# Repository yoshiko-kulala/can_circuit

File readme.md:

# ロボット用can通信基板
このリポジトリはcan通信を用いてロボットのセンサやアクチュエータと通信・制御するための基板が置いてあります。  

各基板ごとに回路図、kicadプロジェクトデータ、サンプルプログラムが含まれます。  
自由に複製してロボットに用いることが出来ます。

can通信のid、内容については下記の各項目で示します。
通信速度は1Mbpsです。

## bumperboard
デジタルのスイッチとADCの信号を読み取ることが出来ます。  
デジタル信号が4つ、ADCは8bitが8チャネルあります。  
メインMCUにはteensy3.2を使用、can通信の通信内容は以下の通りです。  
### 0x001
| buf[1] | 中身 | 備考 |
| -------- | -------- | -------- |
| buf[0] | デジタル信号 | 4つの入力の論理和 |
### 0x003
| buf[8] | 中身 | 備考 |
| -------- | -------- | -------- |
| buf[0] | A0 | 0~255 |
| buf[1] | A1 |  |
| buf[2] | A2 |  |
| buf[3] | A3 |  |
| buf[4] | A4 |  |
| buf[5] | A5 |  |
| buf[6] | A6 |  |
| buf[7] | A7 |  |

## encoderboard  
インクリメントエンコーダを読み取り、回転速度と積分量を返します。  
エンコーダは最大3つまで搭載できます。
MCUにはstm32f303k8を使用し、ハードウェアデコーダを用いてエンコーダの読み取りを行っています。
can通信の内容は以下の通りです。
### 0x301
| buf[8] | 中身 | 備考 |
| -------- | -------- | -------- |
| buf[0] | エンコーダ0のカウント下8bit | 速度は10bit |
| buf[1] | エンコーダ0のカウント上2bitとエンコーダ1のカウント下6bit |  |
| buf[2] | エンコーダ1のカウント下4bitとエンコーダ2のカウント下4bit |  |
| buf[3] | エンコーダ2のカウント下6bit |  |
| buf[4] | 未使用 |  |
| buf[5] | 未使用 |  |
| buf[6] | 未使用 |  |
| buf[7] | 未使用 |  |
### 0x302
| buf[8] | 中身 | 備考 |
| -------- | -------- | -------- |
| buf[0] | エンコーダ0のカウント下8bit | 上下合成して0~65536 |
| buf[1] | エンコーダ0のカウント上8bit |  |
| buf[2] | エンコーダ1のカウント下8bit | 上下合成して0~65536 |
| buf[3] | エンコーダ1のカウント上8bit |  |
| buf[4] | エンコーダ2のカウント下8bit | 上下合成して0~65536 |
| buf[5] | エンコーダ2のカウント上8bit |  |
| buf[6] | 未使用 |  |
| buf[7] | 未使用 |  |

## purin_main_board  
ブザーやジャイロ、コントローラ用の通信口を持った基板  
モータドライバとも接続可能で足回りの駆動系と通信することが出来る  
DJIのDR16と接続することでコントローラとの通信も可能
この基板についてはデバッグ用のcan受信プログラムが書かれている。使途に合わせて自由な内容を受信し、それに合わせてブザーを鳴らしたりモータを動かすことが可能である。

## RIOboard  
myRIOと接続し、can通信とmyRIOをつなげる基板  
myRIOとはGPIO4つとuartで接続されている。
また、myRIOからスレーブコントローラ用へのUSBコネクタも内包している。
この基板もmyRIOからの信号に合わせて自由に通信内容を決めることが出来る。

## stepperboard  
ステッピングモータを駆動させるための基板  
L6470とSPI通信を行い、最大3つのステッピングモータを駆動可能  
電源供給用のコネクタやリミットスイッチの入力コネクタも実装済  
サーボを1つまで接続し動作させることが出来る  
can通信の内容は以下の通り  
### 0x2F1
| buf[8] | 中身 | 備考 |
| -------- | -------- | -------- |
| buf[0] | 現在のx軸(左右)の下8bit | x上限は4374  センターは2768 |
| buf[1] | 現在のx軸(左右)の上8bit | 下限が左 |
| buf[2] | 現在のy軸(上下)の下8bit | y上限は4050 |
| buf[3] | 現在のy軸(上下)の上8bit | 下限が上 |
| buf[4] | 現在のz軸(前後)の下8bit | z上限は31500 |
| buf[5] | 現在のz軸(前後)の上8bit | 下限が後 |
| buf[6] | ハンド | 1で閉じてる、0で開いてる |
| buf[7] | 未使用 |  |
### 0x2F2
| buf[8] | 中身 | 備考 |
| -------- | -------- | -------- |
| buf[0] | 目標のx軸(左右)の下8bit | x上限は4374  センターは2768 |
| buf[1] | 目標のx軸(左右)の上8bit | 下限が左 |
| buf[2] | 目標のy軸(上下)の下8bit | y上限は4050 |
| buf[3] | 目標のy軸(上下)の上8bit | 下限が上 |
| buf[4] | 目標のz軸(前後)の下8bit | z上限は31500 |
| buf[5] | 目標のz軸(前後)の上8bit | 下限が後 |
| buf[6] | ホーム復帰 | 1でホーム復帰 |
| buf[7] | 未使用 |  |
### 0x2F3
msg.len=1
| buf[1] | 中身 | 備考 |
| -------- | -------- | -------- |
| buf[0] | ハンド開閉 | 0が閉じている、1が開いてる |

## UIboard  
デジタルの信号入力が4つ、ws2812bというマイコン内蔵RGBLEDの制御信号を出すことが出来る  
非常停止スイッチが取り付けられることを想定してcanのidは0となっており最優先で信号が送られる。  
通信内容は以下の通り。  
### 0x000
| buf[8] | 中身 | 備考 |
| -------- | -------- | -------- |
| buf[0] | 状態 | 現在のライトの色 |
| buf[1] | 非常停止スイッチ | 押下状態で0 |
| buf[2] | リセットスイッチ | 押下状態で0 |
| buf[3] | 起動スイッチ | 押下状態で0 |
| buf[4] | 空き | 押下状態で0 |
| buf[5] | 未使用 |  |
| buf[6] | 未使用 |  |
| buf[7] | 未使用 |  |

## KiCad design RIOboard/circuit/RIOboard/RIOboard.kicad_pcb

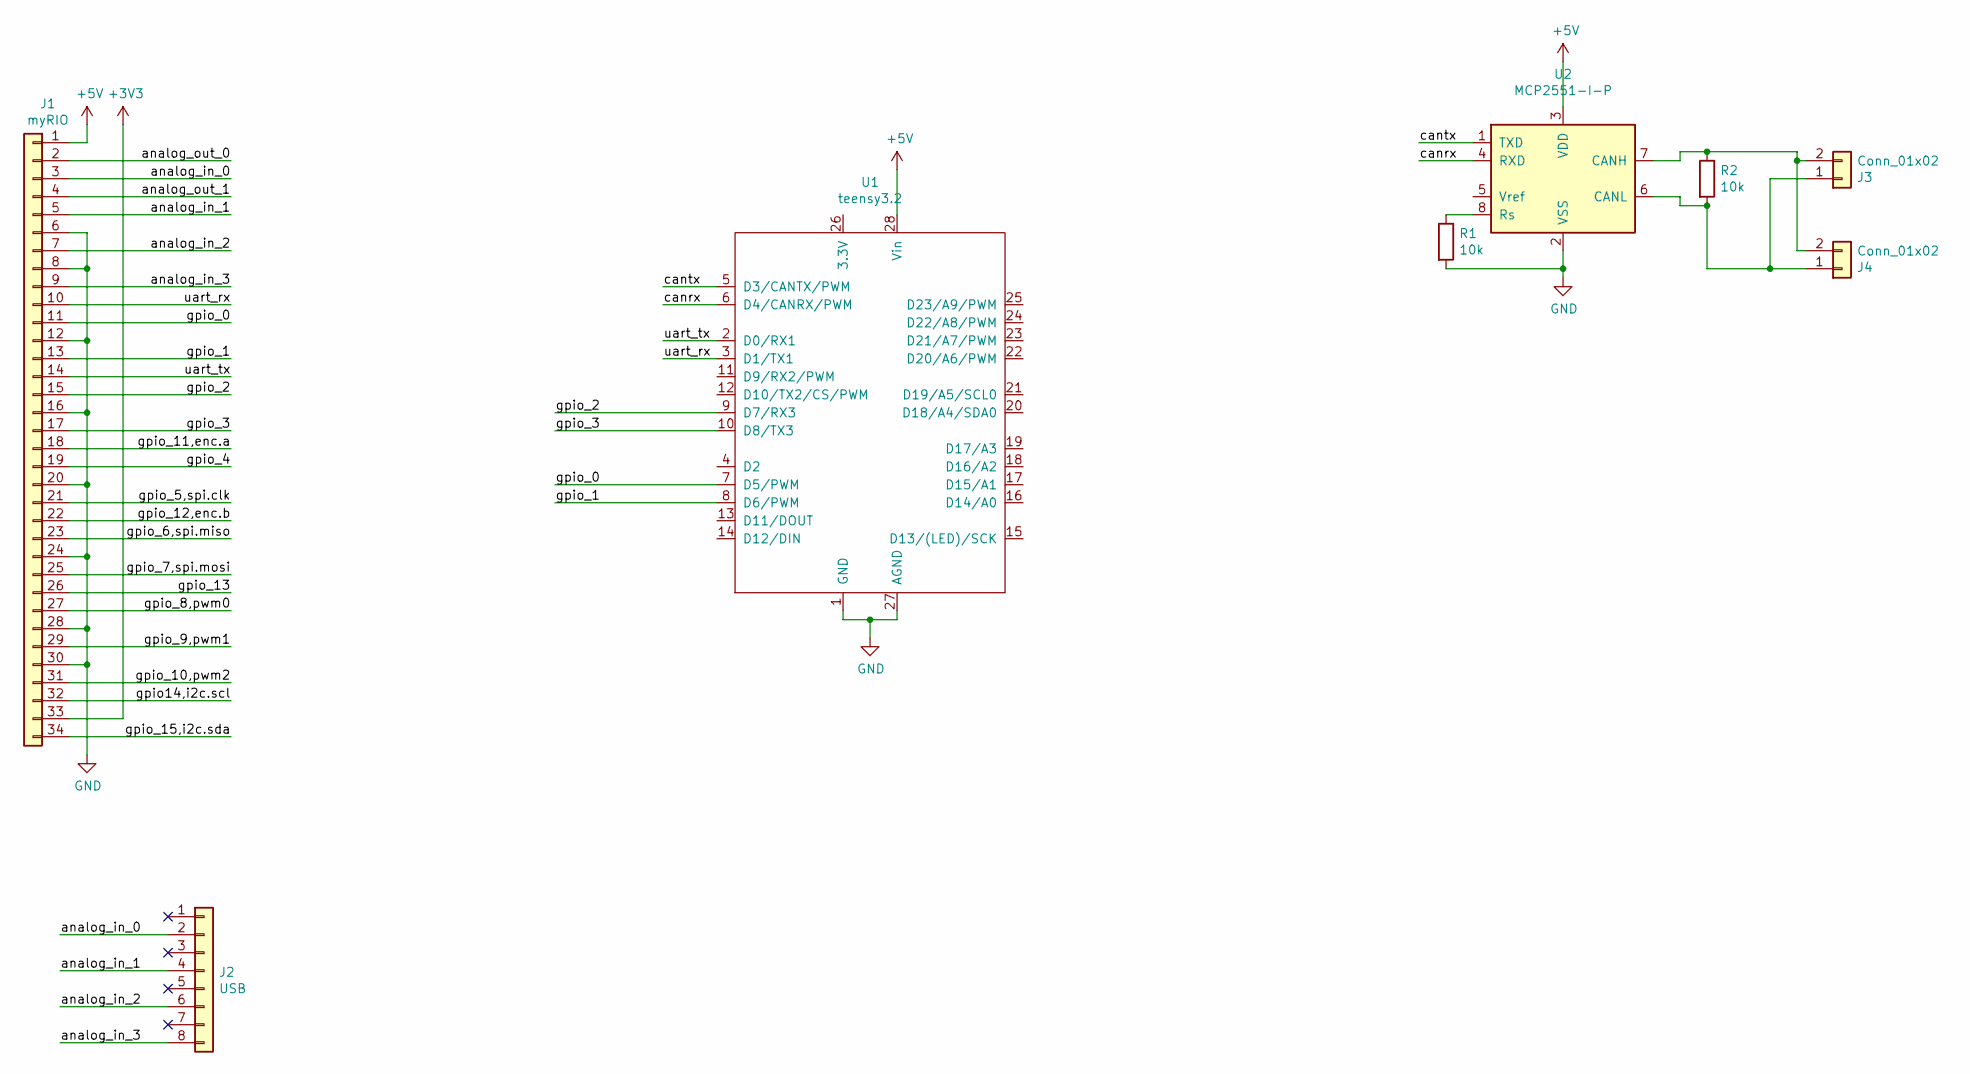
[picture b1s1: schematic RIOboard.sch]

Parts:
J1: myRIO; yokodasipinsoket
J2: USB; PinHeader_2x04_P2.54mm_Vertical
J3, J4: Conn_01x02; JST_XH_B2B-XH-A_1x02_P2.50mm_Vertical
R1, R2: 10k; R_Axial_DIN0207_L6.3mm_D2.5mm_P10.16mm_Horizontal
U1: teensy3.2
U2: MCP2551-I-P; DIP-8_W7.62mm

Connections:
+3V3: J1.33
+5V: J1.1, U1.28 (Vin), U2.3 (VDD); also elsewhere on the board
/analog_in_0: J1.3, J2.2
/analog_in_1: J1.5, J2.4
/analog_in_2: J1.7, J2.6
/analog_in_3: J1.9, J2.8
/analog_out_0: J1.2
/analog_out_1: J1.4
/canrx: U1.6 (D4/CANRX/PWM), U2.4 (RXD)
/cantx: U1.5 (D3/CANTX/PWM), U2.1 (TXD)
/gpio14,i2c.scl: J1.32
/gpio_0: J1.11, U1.7 (D5/PWM)
/gpio_1: J1.13, U1.8 (D6/PWM)
/gpio_2: J1.15, U1.9 (D7/RX3)
/gpio_3: J1.17, U1.10 (D8/TX3)
/gpio_4: J1.19
/gpio_5,spi.clk: J1.21
/gpio_6,spi.miso: J1.23
/gpio_7,spi.mosi: J1.25
/gpio_8,pwm0: J1.27
/gpio_9,pwm1: J1.29
/gpio_10,pwm2: J1.31
/gpio_11,enc.a: J1.18
/gpio_12,enc.b: J1.22
/gpio_13: J1.26
/gpio_15,i2c.sda: J1.34
/uart_rx: J1.10, U1.3 (D1/TX1)
/uart_tx: J1.14, U1.2 (D0/RX1)
GND: J1.6, J1.8, J1.12, J1.16, J1.20, J1.24, J1.28, J1.30, R1.2, U1.1 (GND), U1.27 (AGND), U2.2 (VSS); also elsewhere on the board
unnamed 29: U1.11 (D9/RX2/PWM); also elsewhere on the board
unnamed 30: U1.12 (D10/TX2/CS/PWM); also elsewhere on the board
unnamed 32: U1.19 (D17/A3); also elsewhere on the board
unnamed 33: U1.18 (D16/A2); also elsewhere on the board
unnamed 34: U1.17 (D15/A1); also elsewhere on the board
unnamed 35: U1.16 (D14/A0); also elsewhere on the board
unnamed: J3.1, J4.1, R2.2, U2.6 (CANL)
unnamed: J3.2, J4.2, R2.1, U2.7 (CANH)
unnamed: R1.1, U2.8 (Rs)

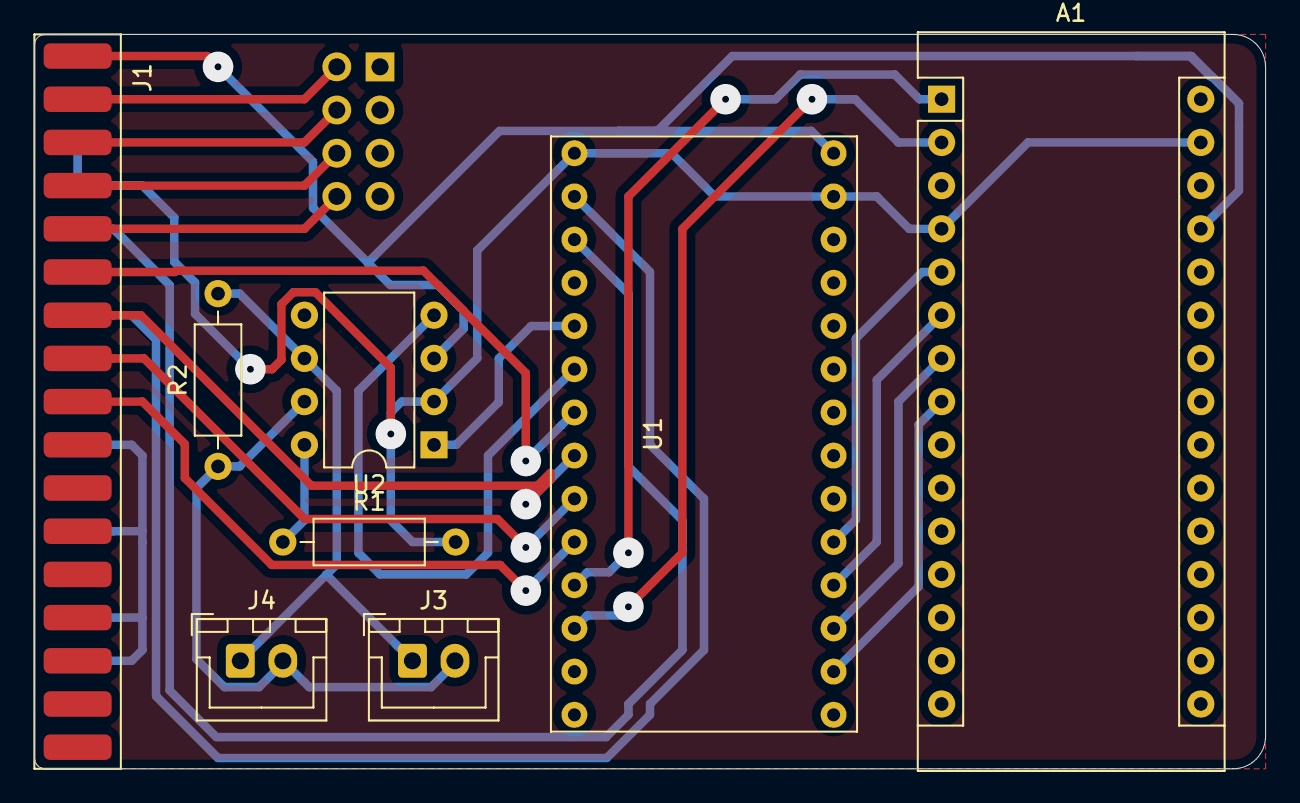
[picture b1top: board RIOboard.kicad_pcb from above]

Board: 2 copper layers, 72.4 x 43.2 mm, 9 parts (1 on the bottom side), 23 nets.

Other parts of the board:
A1: Arduino_Nano_v3.x; Arduino_Nano

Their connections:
+5V: A1.27; also elsewhere on the board
GND: A1.4, A1.29; also elsewhere on the board
unnamed 29: A1.1; also elsewhere on the board
unnamed 30: A1.2; also elsewhere on the board
unnamed 32: A1.5; also elsewhere on the board
unnamed 33: A1.6; also elsewhere on the board
unnamed 34: A1.7; also elsewhere on the board
unnamed 35: A1.8; also elsewhere on the board

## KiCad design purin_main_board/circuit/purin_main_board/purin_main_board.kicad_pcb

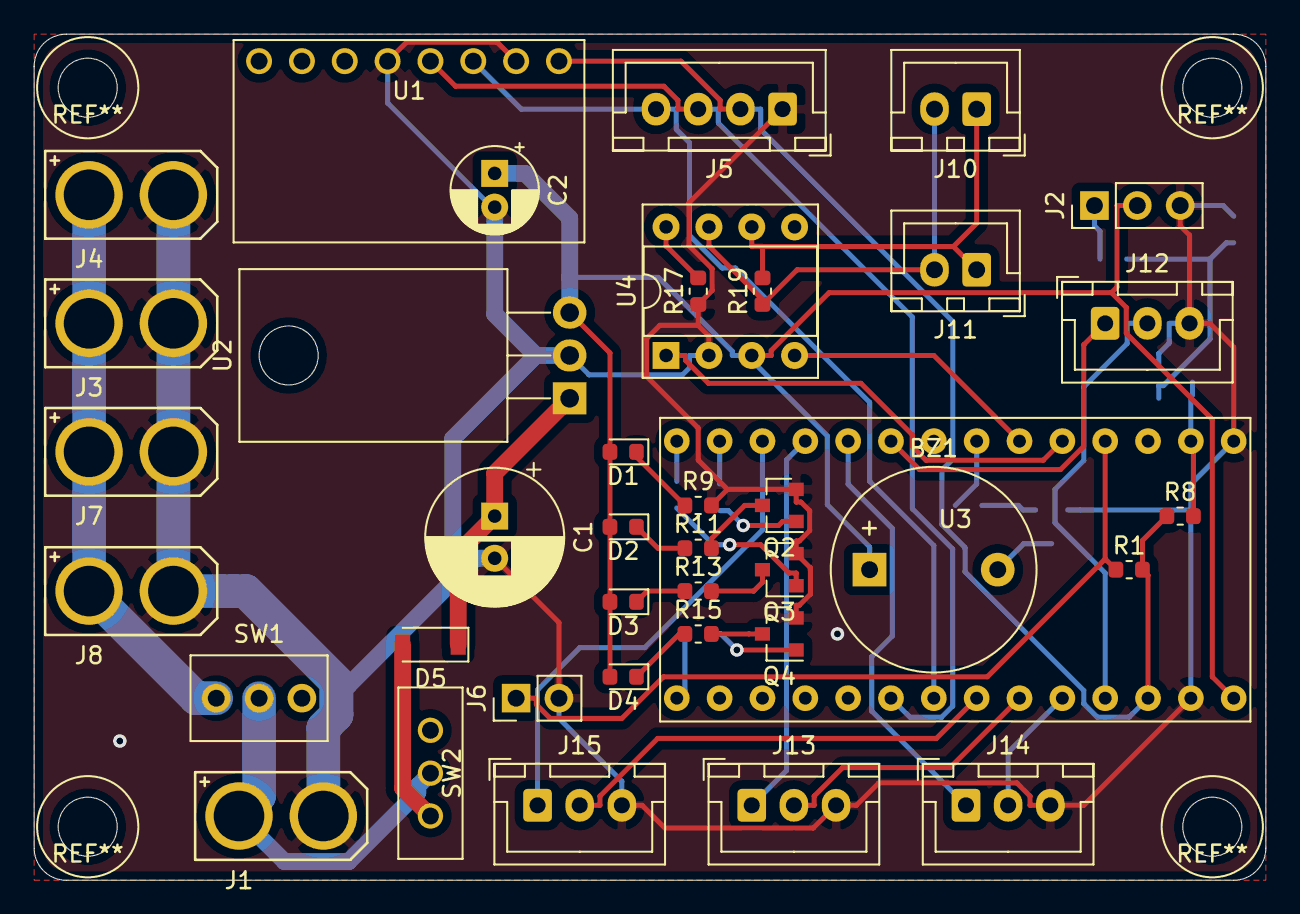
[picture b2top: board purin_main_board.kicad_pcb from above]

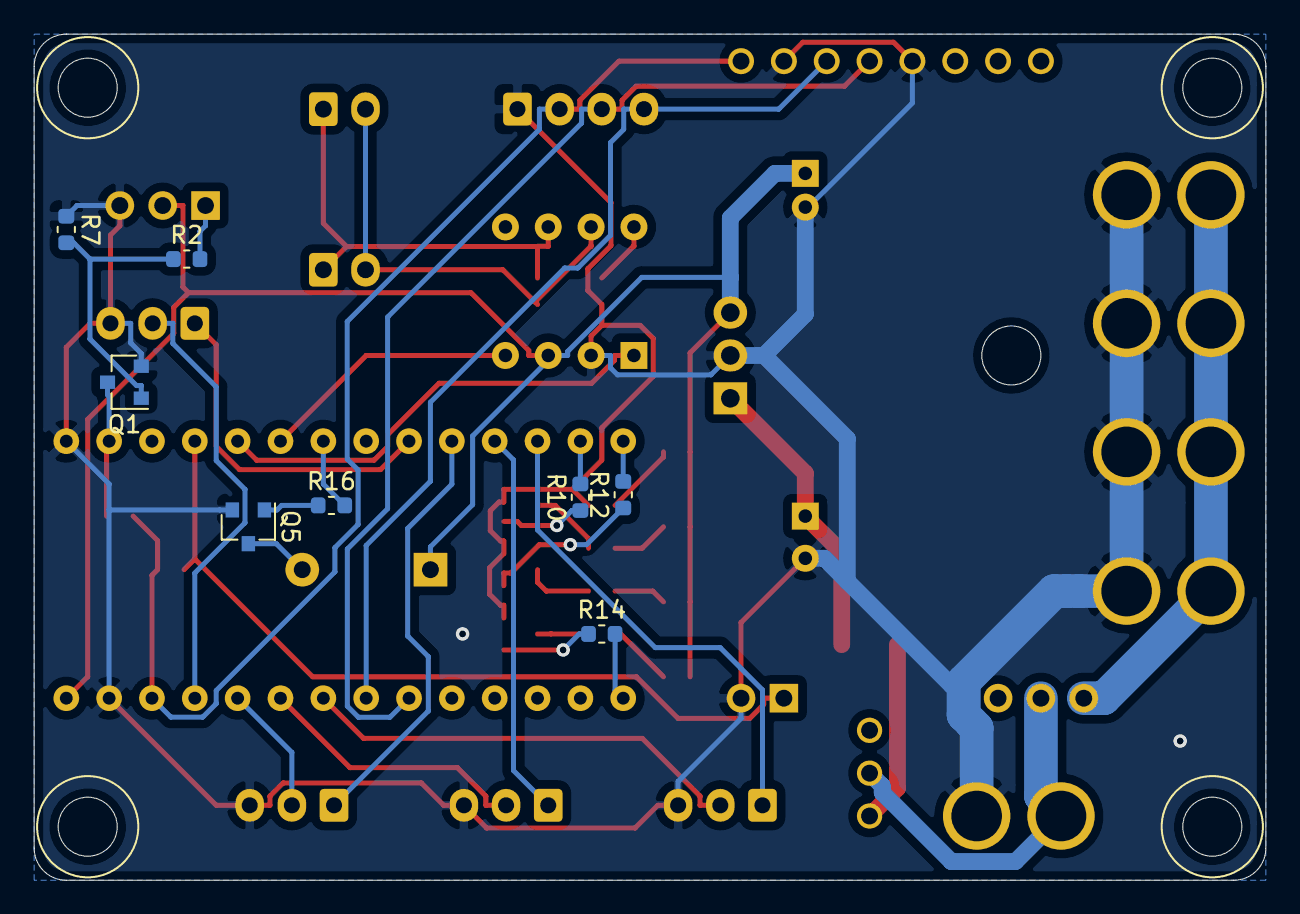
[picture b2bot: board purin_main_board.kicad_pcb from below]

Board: 2 copper layers, 73.0 x 50.2 mm, 47 parts (8 on the bottom side), 42 nets.

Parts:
BZ1: Buzzer; Buzzer_12x9.5RM7.6
C1: 220u; CP_Radial_D8.0mm_P2.50mm
C2: 100u; CP_Radial_D5.0mm_P2.00mm
D1: LED_power; LED_0603_1608Metric
D2: LED1; LED_0603_1608Metric
D3: LED2; LED_0603_1608Metric
D4: LED3; LED_0603_1608Metric
D5: 1N4148W; D_SOD-123
J1: battery; xt30u-f
J2: uart1_rx; PinHeader_1x03_P2.54mm_Vertical
J3, J4, J7, J8: Conn_01x02; xt30u-f
J5: i2c; JST_XH_B4B-XH-A_1x04_P2.50mm_Vertical
J6: user_sw; PinHeader_1x02_P2.54mm_Vertical
J10: can1; JST_XH_B2B-XH-A_1x02_P2.50mm_Vertical
J11: can2; JST_XH_B2B-XH-A_1x02_P2.50mm_Vertical
J12: motor1; JST_XH_B3B-XH-A_1x03_P2.50mm_Vertical
J13: motor3; JST_XH_B3B-XH-A_1x03_P2.50mm_Vertical
J14: motor2; JST_XH_B3B-XH-A_1x03_P2.50mm_Vertical
J15: motor4; JST_XH_B3B-XH-A_1x03_P2.50mm_Vertical
Q1, Q2, Q3, Q4, Q5: BSS138; SOT-23
R1, R7, R17: 10k; R_0603_1608Metric
R2, R10, R12, R14, R16: 1k; R_0603_1608Metric
R8: 4k7; R_0603_1608Metric
R9, R11, R13, R15: 100; R_0603_1608Metric
R19: 120; R_0603_1608Metric
SW1: SW_Push_SPDT; toggle
SW2: SW_Push_SPDT; mini_sw
U1: BNO055
U2: L7805; TO-220-3_Horizontal_TabDown
U3: teensy3.2
U4: MCP2551-I-P; DIP-8_W7.62mm_Socket

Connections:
+3V3: J5.2, R1.2, R8.1, U1.1, U3.26
+5V: BZ1.1, C2.1, D1.2, D2.2, D3.2, D4.2, J2.2, U2.3, U3.28, U4.3
+BATT: J3.1, J4.1, J7.1, J8.1, SW1.3
/buzzer: R16.2, U3.7
/canH: J10.2, J11.2, R19.1, U4.7
/canL: J10.1, J11.1, R19.2, U4.6
/canrx: U3.6, U4.4
/cantx: U3.5, U4.1
/dir1: J12.1, U3.9
/dir2: J14.1, U3.10
/dir3: J13.1, U3.11
/dir4: J15.1, U3.12
/led1: R10.2, U3.13
/led2: R12.2, U3.14
/led3: R14.2, U3.15
/pwm1: J12.2, U3.25
/pwm2: J14.2, U3.24
/pwm3: J13.2, U3.23
/pwm4: J15.2, U3.22
/rx1: Q1.3, R8.2, U3.2
/scl: J5.4, U1.3, U3.21
/sda: J5.3, U1.4, U3.20
/user_sw: J6.1, R1.1, U3.4
GND: C1.2, C2.2, J1.2, J2.3, J3.2, J4.2, J5.1, J6.2, J7.2, J8.2, J12.3, J13.3, J14.3, J15.3, Q1.2, Q2.2, Q3.2, Q4.2, Q5.2, R7.1, R9.2, R17.1, U1.2, U1.5, U2.2, U3.1, U3.27, U4.2
unnamed: BZ1.2, Q5.3
unnamed: C1.1, D5.1, U2.1
unnamed: D1.1, R9.1
unnamed: D2.1, R11.1
unnamed: D3.1, R13.1
unnamed: D4.1, R15.1
unnamed: D5.2, SW2.1
unnamed: J1.1, SW1.2, SW2.2
unnamed: J2.1, R2.2
unnamed: Q1.1, R2.1, R7.2
unnamed: Q2.1, R10.1
unnamed: Q2.3, R11.2
unnamed: Q3.1, R12.1
unnamed: Q3.3, R13.2
unnamed: Q4.1, R14.1
unnamed: Q4.3, R15.2
unnamed: Q5.1, R16.1
unnamed: R17.2, U4.8

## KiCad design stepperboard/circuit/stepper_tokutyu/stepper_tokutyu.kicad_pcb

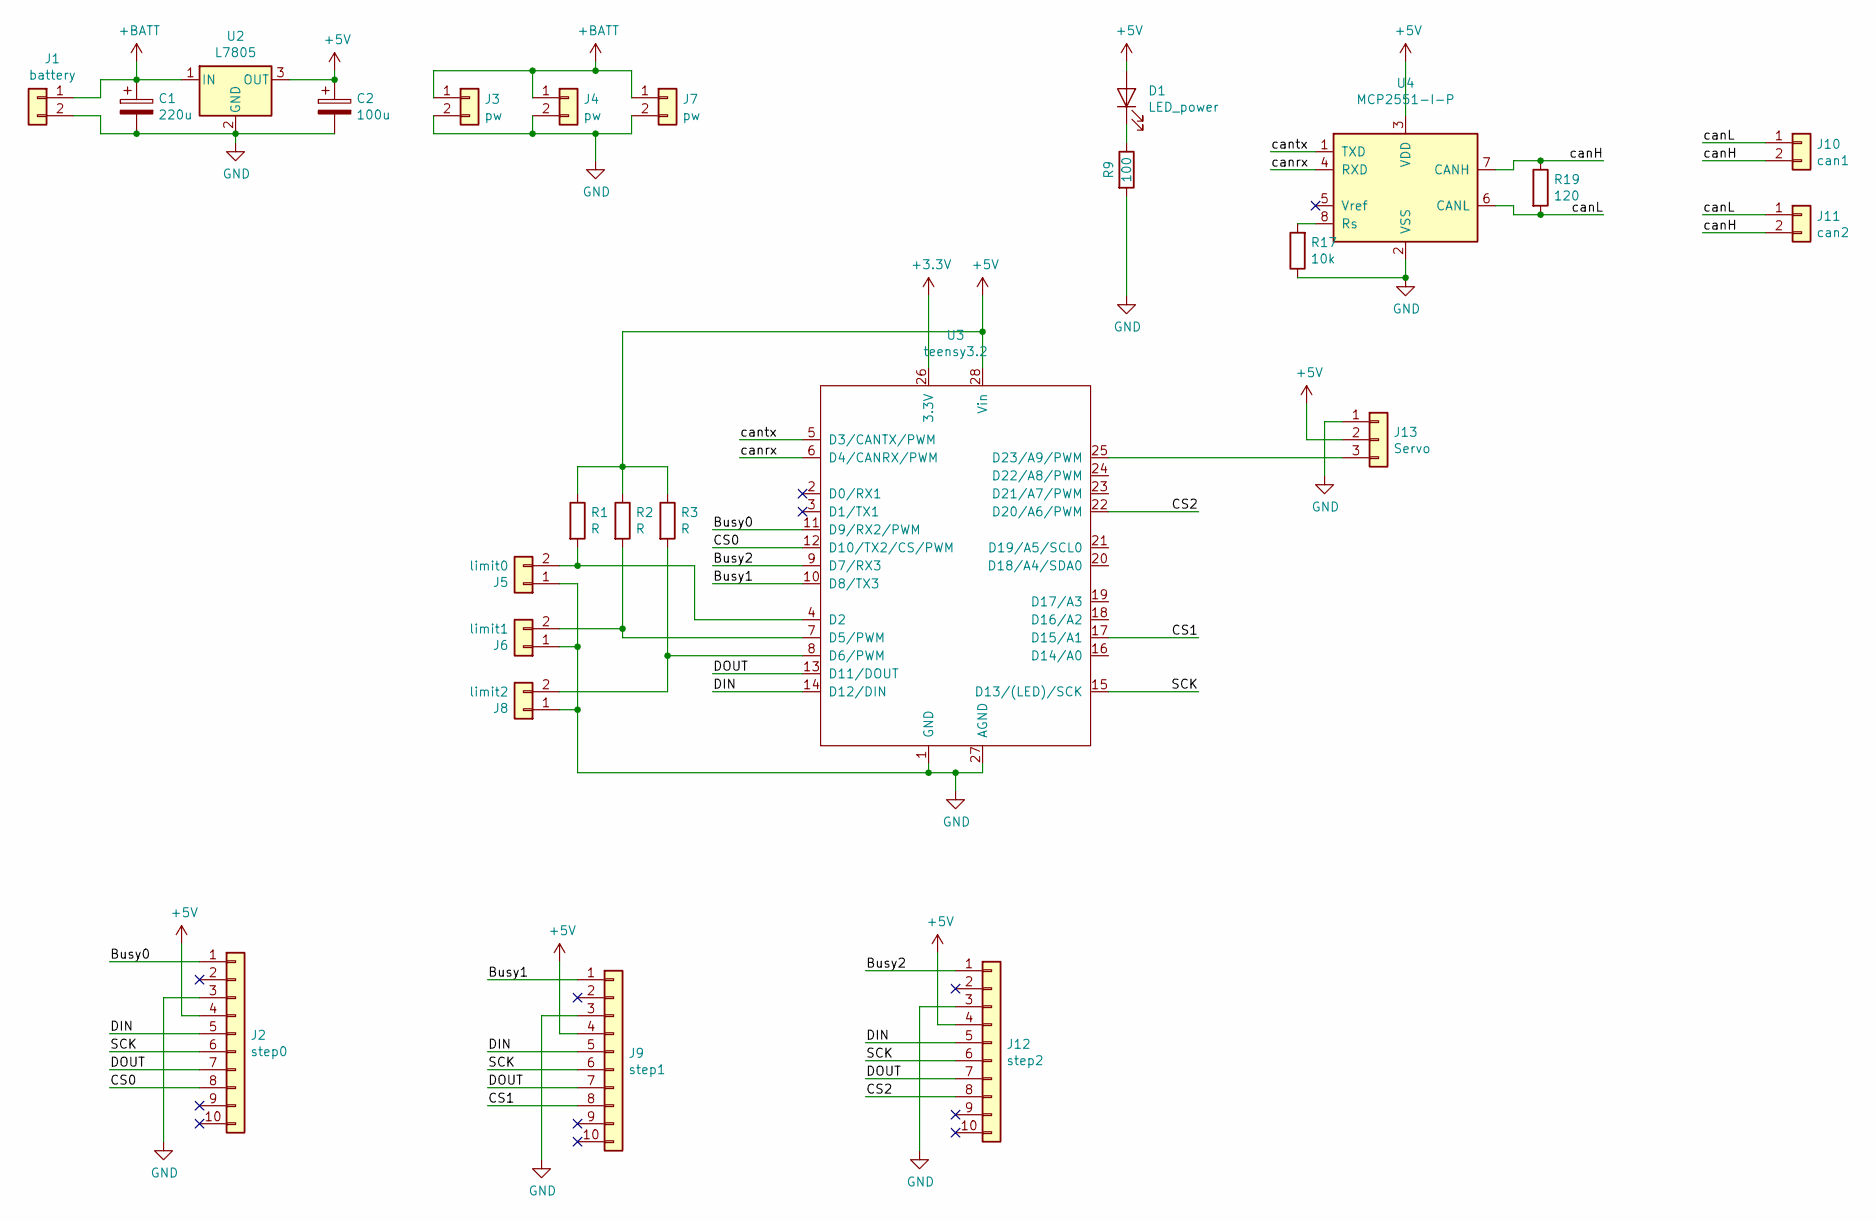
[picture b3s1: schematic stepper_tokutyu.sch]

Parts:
C1: 220u; CP_Radial_D8.0mm_P2.50mm
C2: 100u; CP_Radial_D5.0mm_P2.00mm
D1: LED_power; LED_D5.0mm
J1: battery; JST_XH_B2B-XH-A_1x02_P2.50mm_Vertical
J2: step0; IDC-Header_2x05_P2.54mm_Vertical
J3, J4, J7: pw; JST_XH_B2B-XH-A_1x02_P2.50mm_Vertical
J5: limit0; JST_XH_B2B-XH-A_1x02_P2.50mm_Vertical
J6: limit1; JST_XH_B2B-XH-A_1x02_P2.50mm_Vertical
J8: limit2; JST_XH_B2B-XH-A_1x02_P2.50mm_Vertical
J9: step1; IDC-Header_2x05_P2.54mm_Vertical
J10: can1; JST_XH_B2B-XH-A_1x02_P2.50mm_Vertical
J11: can2; JST_XH_B2B-XH-A_1x02_P2.50mm_Vertical
J12: step2; IDC-Header_2x05_P2.54mm_Vertical
J13: Servo; JST_XH_B3B-XH-A_1x03_P2.50mm_Vertical
R1, R2, R3: R; R_0603_1608Metric
R9: 100; R_0603_1608Metric
R17: 10k; R_0603_1608Metric
R19: 120; R_0603_1608Metric
U2: L7805; TO-220-3_Vertical
U3: teensy3.2
U4: MCP2551-I-P; DIP-8_W7.62mm_Socket

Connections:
+3V3: U3.26 (3.3V)
+5V: C2.1, D1.2 (A), J2.4, J9.4, J12.4, J13.2, R1.1, R2.1, R3.1, U2.3 (OUT), U3.28 (Vin), U4.3 (VDD)
+BATT: C1.1, J1.1, J3.1, J4.1, J7.1, U2.1 (IN)
/Busy0: J2.1, U3.11 (D9/RX2/PWM)
/Busy1: J9.1, U3.10 (D8/TX3)
/Busy2: J12.1, U3.9 (D7/RX3)
/CS0: J2.8, U3.12 (D10/TX2/CS/PWM)
/CS1: J9.8, U3.17 (D15/A1)
/CS2: J12.8, U3.22 (D20/A6/PWM)
/DIN: J2.5, J9.5, J12.5, U3.14 (D12/DIN)
/DOUT: J2.7, J9.7, J12.7, U3.13 (D11/DOUT)
/SCK: J2.6, J9.6, J12.6, U3.15 (D13/(LED)/SCK)
/canH: J10.2, J11.2, R19.1, U4.7 (CANH)
/canL: J10.1, J11.1, R19.2, U4.6 (CANL)
/canrx: U3.6 (D4/CANRX/PWM), U4.4 (RXD)
/cantx: U3.5 (D3/CANTX/PWM), U4.1 (TXD)
GND: C1.2, C2.2, J1.2, J2.3, J3.2, J4.2, J5.1, J6.1, J7.2, J8.1, J9.3, J12.3, J13.1, R9.2, R17.1, U2.2 (GND), U3.1 (GND), U3.27 (AGND), U4.2 (VSS)
unnamed: D1.1 (K), R9.1
unnamed: J5.2, R1.2, U3.4 (D2)
unnamed: J6.2, R2.2, U3.7 (D5/PWM)
unnamed: J8.2, R3.2, U3.8 (D6/PWM)
unnamed: J13.3, U3.25 (D23/A9/PWM)
unnamed: R17.2, U4.8 (Rs)

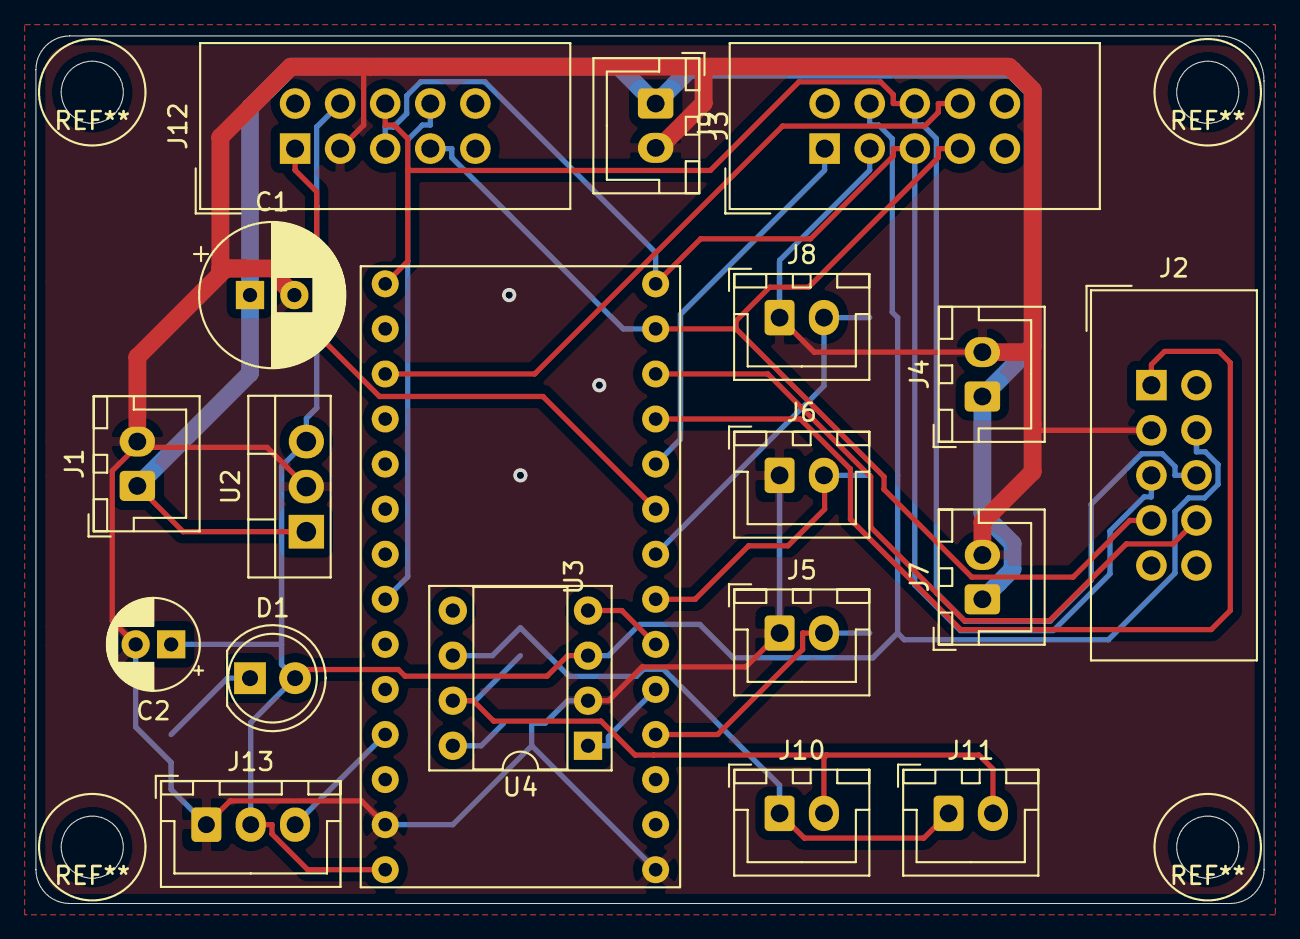
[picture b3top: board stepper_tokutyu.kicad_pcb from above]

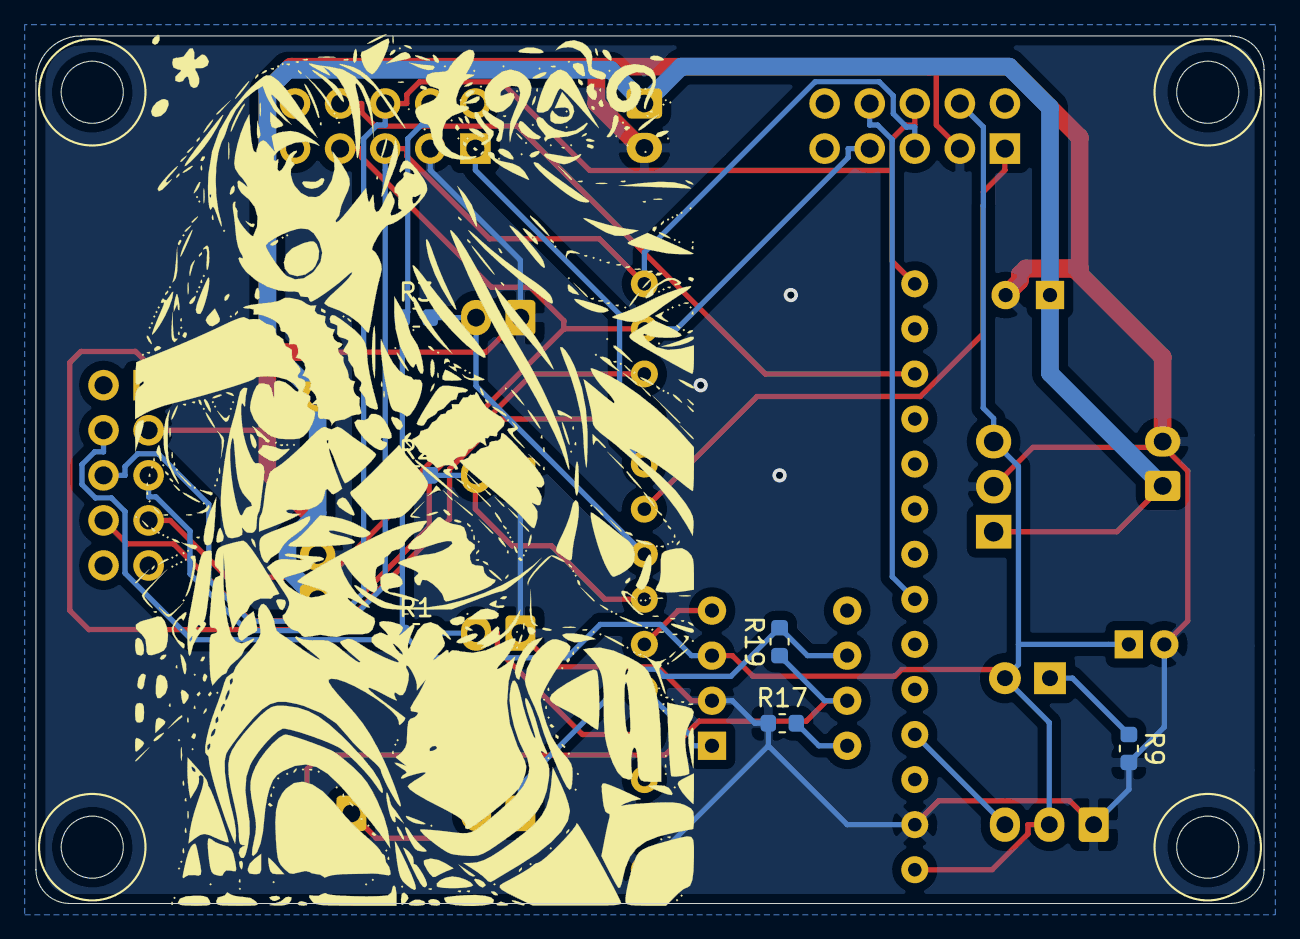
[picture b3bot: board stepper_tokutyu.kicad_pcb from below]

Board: 2 copper layers, 69.2 x 48.9 mm, 25 parts (6 on the bottom side), 22 nets.

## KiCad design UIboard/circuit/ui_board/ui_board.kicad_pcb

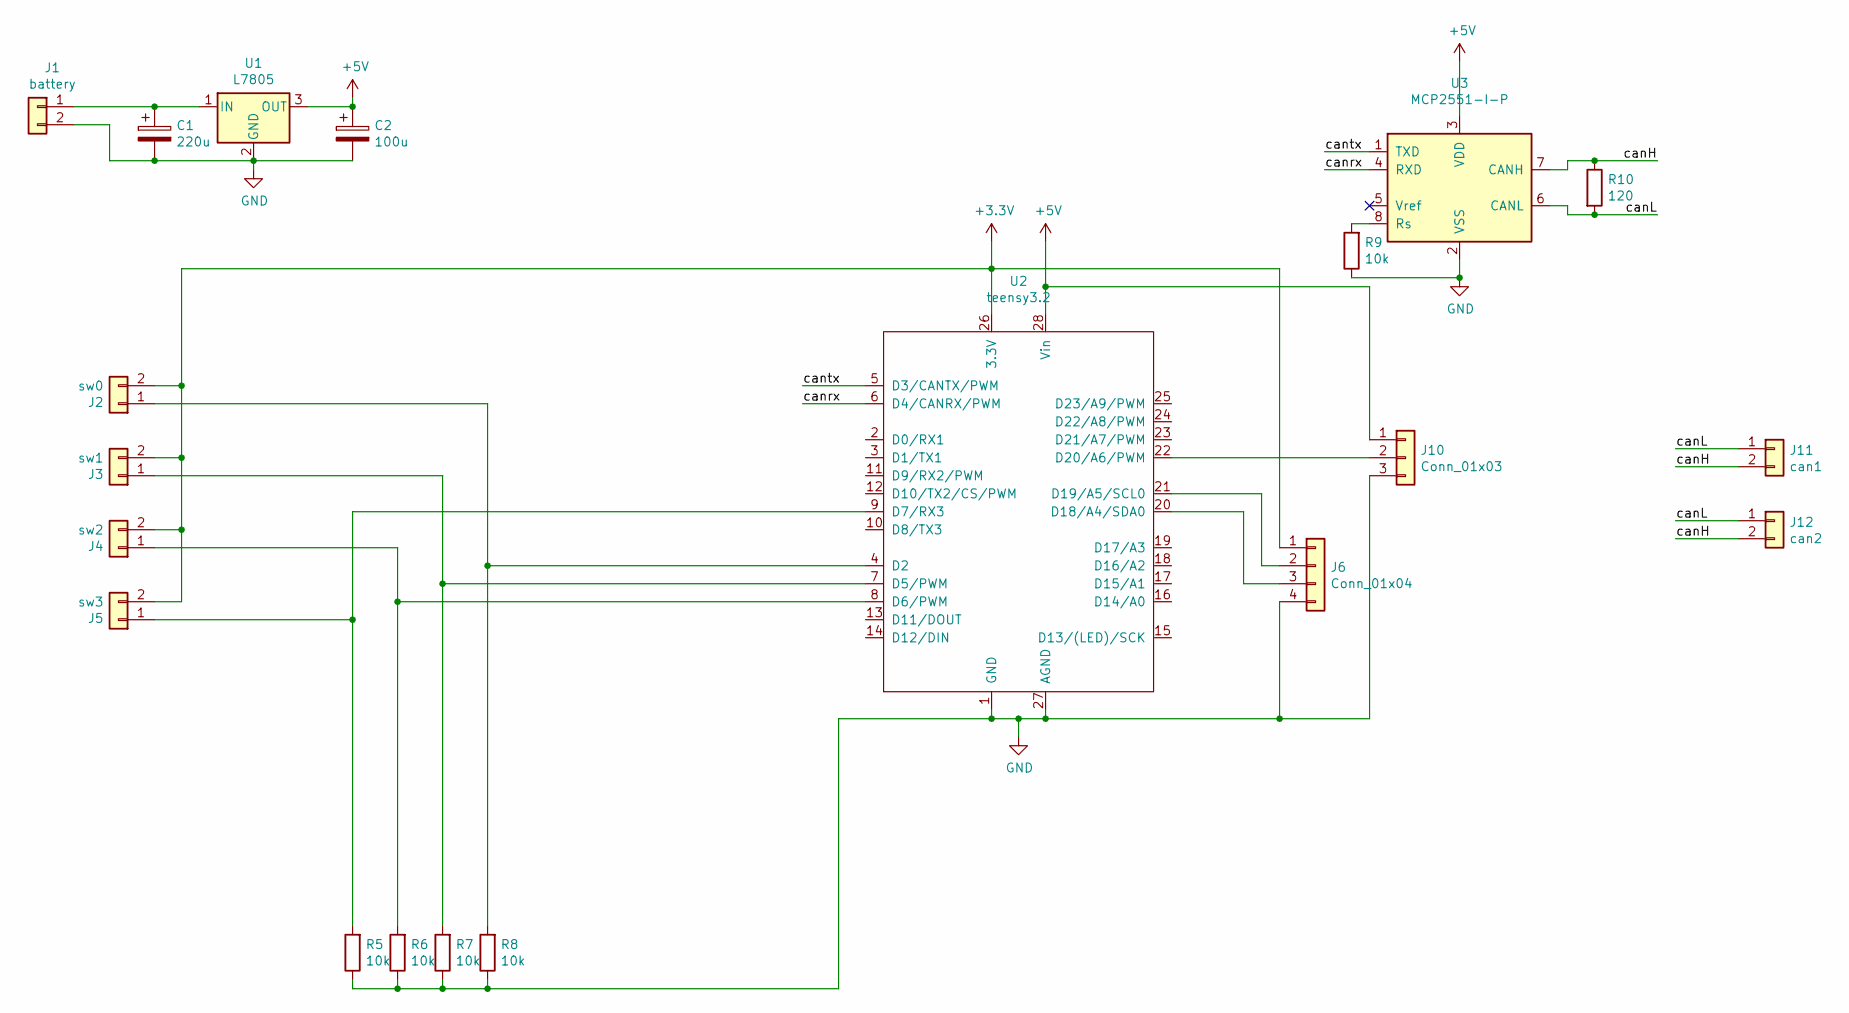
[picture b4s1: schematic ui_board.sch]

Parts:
C1: 220u; CP_Radial_D8.0mm_P2.50mm
C2: 100u; CP_Radial_D5.0mm_P2.00mm
J1: battery; JST_XH_B2B-XH-A_1x02_P2.50mm_Vertical
J2: sw0; JST_XH_B2B-XH-A_1x02_P2.50mm_Vertical
J3: sw1; JST_XH_B2B-XH-A_1x02_P2.50mm_Vertical
J4: sw2; JST_XH_B2B-XH-A_1x02_P2.50mm_Vertical
J5: sw3; JST_XH_B2B-XH-A_1x02_P2.50mm_Vertical
J6: Conn_01x04; JST_XH_B4B-XH-A_1x04_P2.50mm_Vertical
J10: Conn_01x03; JST_XH_B3B-XH-A_1x03_P2.50mm_Vertical
J11: can1; JST_XH_B2B-XH-A_1x02_P2.50mm_Vertical
J12: can2; JST_XH_B2B-XH-A_1x02_P2.50mm_Vertical
R5, R6, R7, R8, R9: 10k; R_Axial_DIN0207_L6.3mm_D2.5mm_P10.16mm_Horizontal
R10: 120; R_Axial_DIN0207_L6.3mm_D2.5mm_P10.16mm_Horizontal
U1: L7805; TO-220-3_Vertical
U2: teensy3.2
U3: MCP2551-I-P; DIP-8_W7.62mm_Socket

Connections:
+3V3: J2.2, J3.2, J4.2, J5.2, J6.1, U2.26 (3.3V)
+5V: C2.1, J10.1, U1.3 (OUT), U2.28 (Vin), U3.3 (VDD)
/canH: J11.2, J12.2, R10.1, U3.7 (CANH)
/canL: J11.1, J12.1, R10.2, U3.6 (CANL)
/canrx: U2.6 (D4/CANRX/PWM), U3.4 (RXD)
/cantx: U2.5 (D3/CANTX/PWM), U3.1 (TXD)
GND: C1.2, C2.2, J1.2, J6.4, J10.3, R5.1, R6.1, R7.1, R8.1, R9.1, U1.2 (GND), U2.1 (GND), U2.27 (AGND), U3.2 (VSS)
unnamed: C1.1, J1.1, U1.1 (IN)
unnamed: J2.1, R8.2, U2.4 (D2)
unnamed: J3.1, R7.2, U2.7 (D5/PWM)
unnamed: J4.1, R6.2, U2.8 (D6/PWM)
unnamed: J5.1, R5.2, U2.9 (D7/RX3)
unnamed: J6.2, U2.21 (D19/A5/SCL0)
unnamed: J6.3, U2.20 (D18/A4/SDA0)
unnamed: J10.2, U2.22 (D20/A6/PWM)
unnamed: R9.2, U3.8 (Rs)

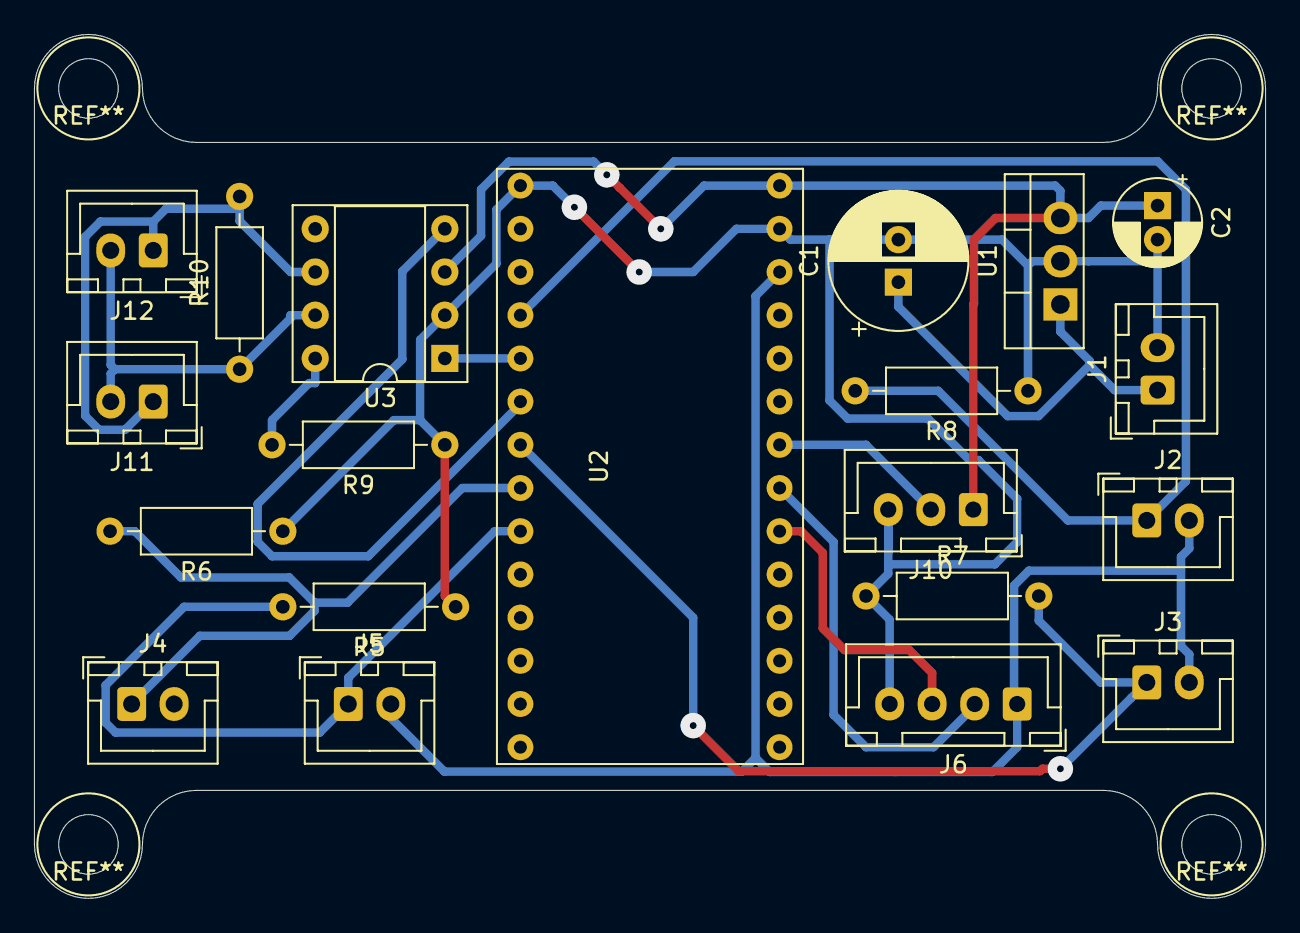
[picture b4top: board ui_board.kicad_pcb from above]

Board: 2 copper layers, 72.4 x 50.8 mm, 20 parts (0 on the bottom side), 16 nets.

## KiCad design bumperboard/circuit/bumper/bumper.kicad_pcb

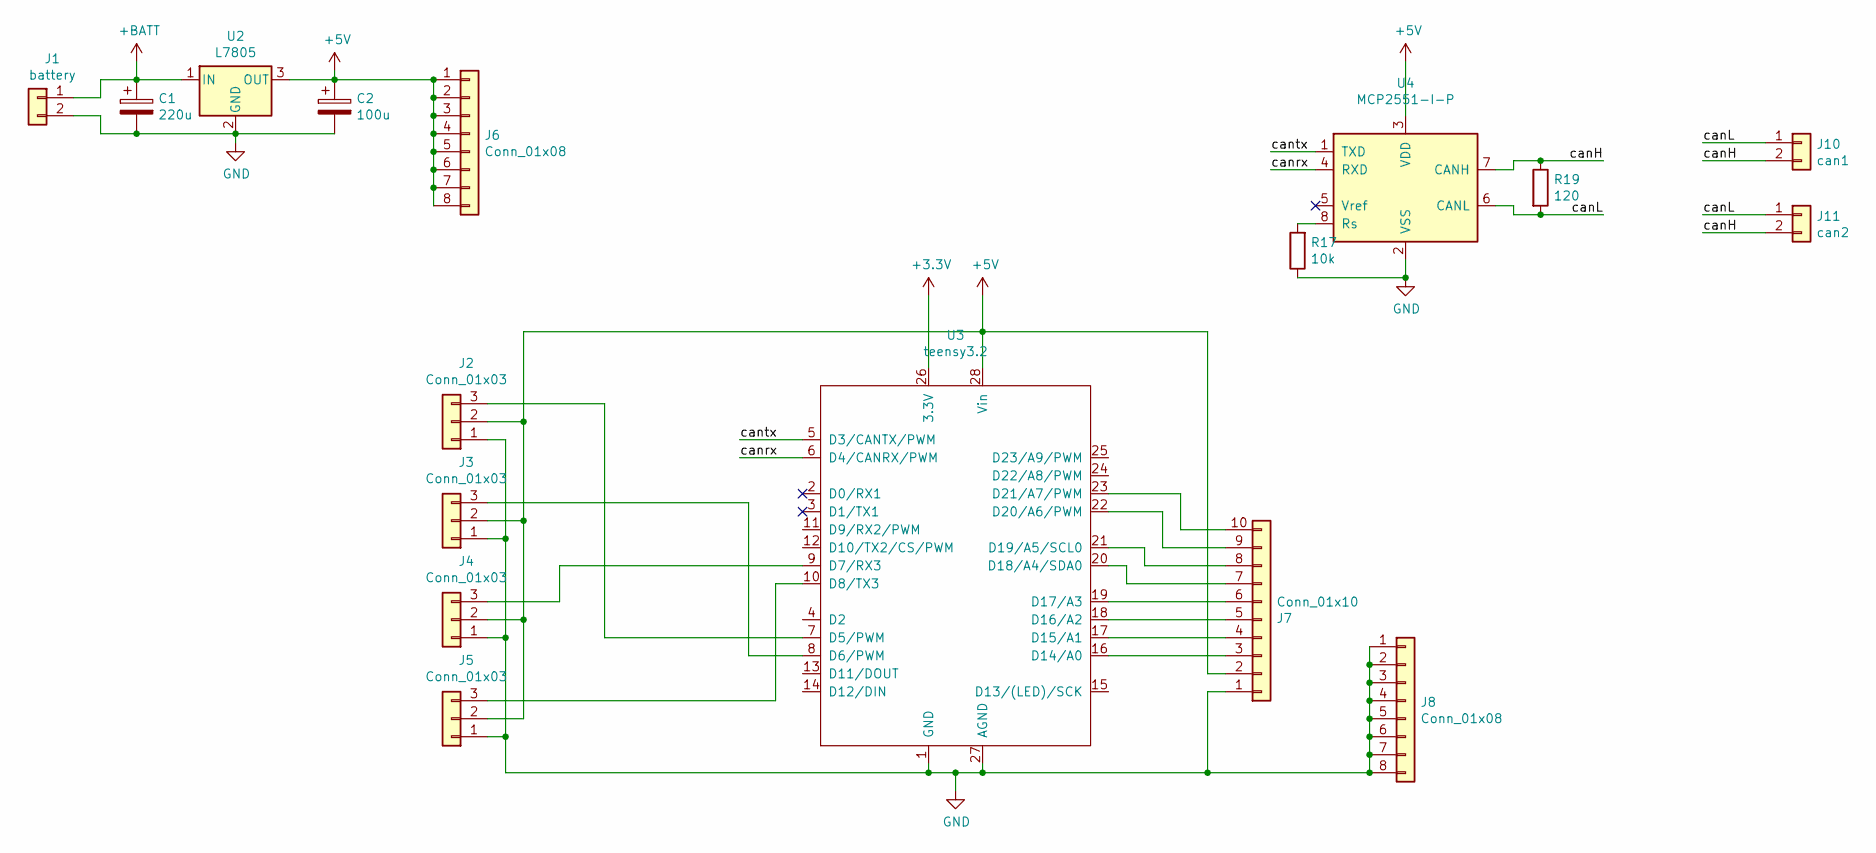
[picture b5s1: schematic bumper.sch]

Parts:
C1: 220u; CP_Radial_D8.0mm_P2.50mm
C2: 100u; CP_Radial_D5.0mm_P2.00mm
J1: battery; JST_XH_B2B-XH-A_1x02_P2.50mm_Vertical
J2, J3, J4, J5: Conn_01x03; JST_XH_B3B-XH-A_1x03_P2.50mm_Vertical
J6, J8: Conn_01x08; PinHeader_1x08_P2.54mm_Vertical
J7: Conn_01x10; PinHeader_1x10_P2.54mm_Vertical
J10: can1; JST_XH_B2B-XH-A_1x02_P2.50mm_Vertical
J11: can2; JST_XH_B2B-XH-A_1x02_P2.50mm_Vertical
R17: 10k; R_Axial_DIN0207_L6.3mm_D2.5mm_P10.16mm_Horizontal
R19: 120; R_Axial_DIN0207_L6.3mm_D2.5mm_P10.16mm_Horizontal
U2: L7805; TO-220-3_Vertical
U3: teensy3.2
U4: MCP2551-I-P; DIP-8_W7.62mm_Socket

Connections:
+3V3: U3.26 (3.3V)
+5V: C2.1, J2.2, J3.2, J4.2, J5.2, J6.1, J6.2, J6.3, J6.4, J6.5, J6.6, J6.7, J6.8, J7.2, U2.3 (OUT), U3.28 (Vin), U4.3 (VDD)
+BATT: C1.1, J1.1, U2.1 (IN)
/canH: J10.2, J11.2, R19.1, U4.7 (CANH)
/canL: J10.1, J11.1, R19.2, U4.6 (CANL)
/canrx: U3.6 (D4/CANRX/PWM), U4.4 (RXD)
/cantx: U3.5 (D3/CANTX/PWM), U4.1 (TXD)
GND: C1.2, C2.2, J1.2, J2.1, J3.1, J4.1, J5.1, J7.1, J8.1, J8.2, J8.3, J8.4, J8.5, J8.6, J8.7, J8.8, R17.1, U2.2 (GND), U3.1 (GND), U3.27 (AGND), U4.2 (VSS)
unnamed: J2.3, U3.7 (D5/PWM)
unnamed: J3.3, U3.8 (D6/PWM)
unnamed: J4.3, U3.9 (D7/RX3)
unnamed: J5.3, U3.10 (D8/TX3)
unnamed: J7.3, U3.16 (D14/A0)
unnamed: J7.4, U3.17 (D15/A1)
unnamed: J7.5, U3.18 (D16/A2)
unnamed: J7.6, U3.19 (D17/A3)
unnamed: J7.7, U3.20 (D18/A4/SDA0)
unnamed: J7.8, U3.21 (D19/A5/SCL0)
unnamed: J7.9, U3.22 (D20/A6/PWM)
unnamed: J7.10, U3.23 (D21/A7/PWM)
unnamed: R17.2, U4.8 (Rs)

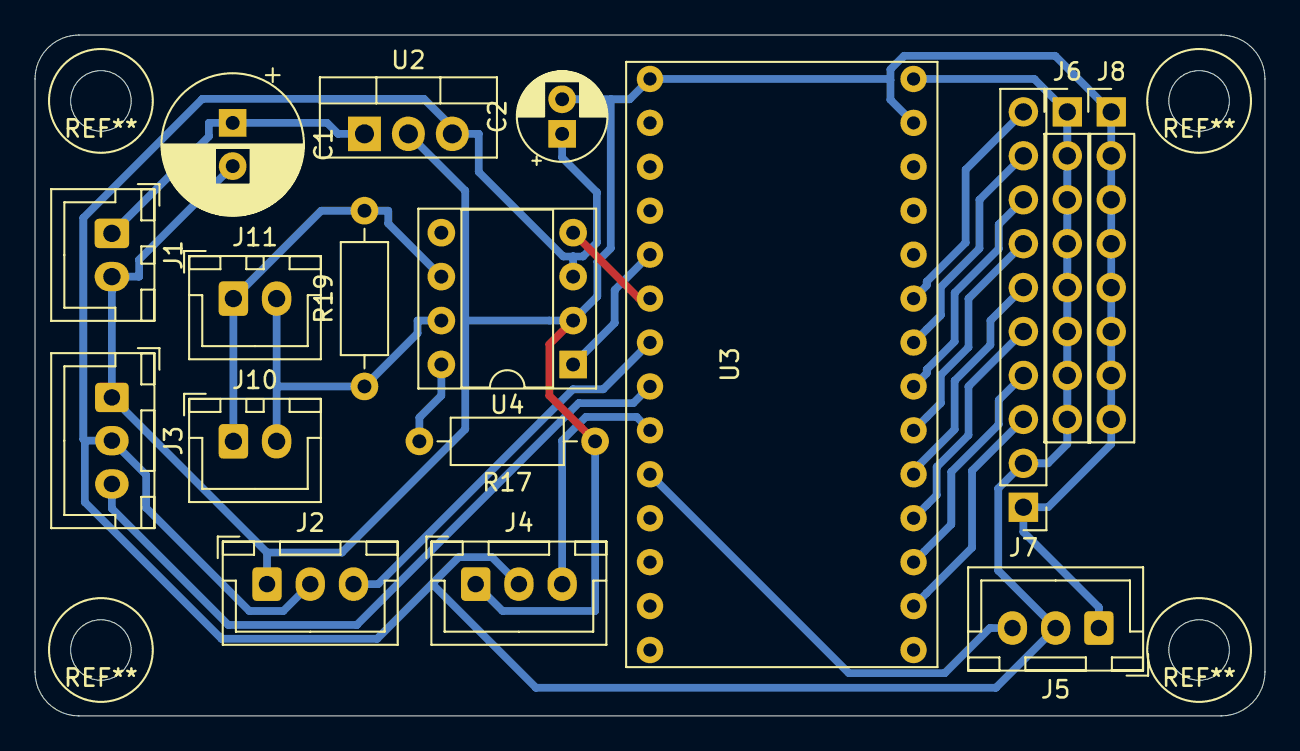
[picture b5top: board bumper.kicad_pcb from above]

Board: 2 copper layers, 71.1 x 39.4 mm, 17 parts (0 on the bottom side), 20 nets.
